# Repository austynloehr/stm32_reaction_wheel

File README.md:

# STM32 Reaction Wheel Development

This repo is used to store all development information for STM32 reaction wheel project.

## Components
- **MCU:** STM32F412CGU6
- **Motor:**  REV Neo 550 (Brushless)
- **Motor Controller:** VESC EDU
- **CAN Transceiver:** NXP TJA1051/T3
- **IMU:** MPU-6050
- **BLE:** HC-05

## Project Structure

- Hardware: All hardware design files for this project
    - Balance_Controller: All KiCAD design files  for controller PCB
    - Reaction_Wheel: All NX CAD files for this project
- Logs: Bluetooth data logs
- ReactionWheel_F412: STM32CubeIDE project, contains all code for MCU
    - Core: Core source code
    - Drivers: STM32 HAL drivers
    - Middlewares: External libraries
- Resources: Markdowns and datasheets
- Scripts: Scripts useful for design and data logging

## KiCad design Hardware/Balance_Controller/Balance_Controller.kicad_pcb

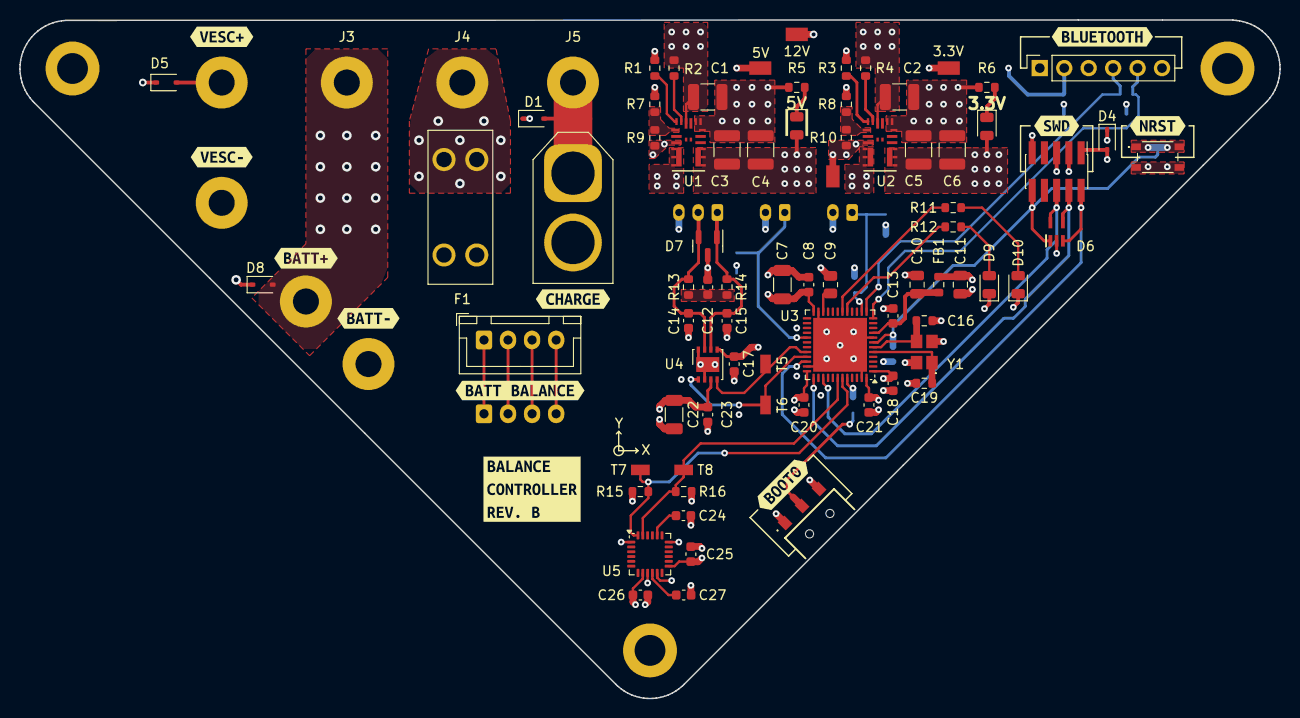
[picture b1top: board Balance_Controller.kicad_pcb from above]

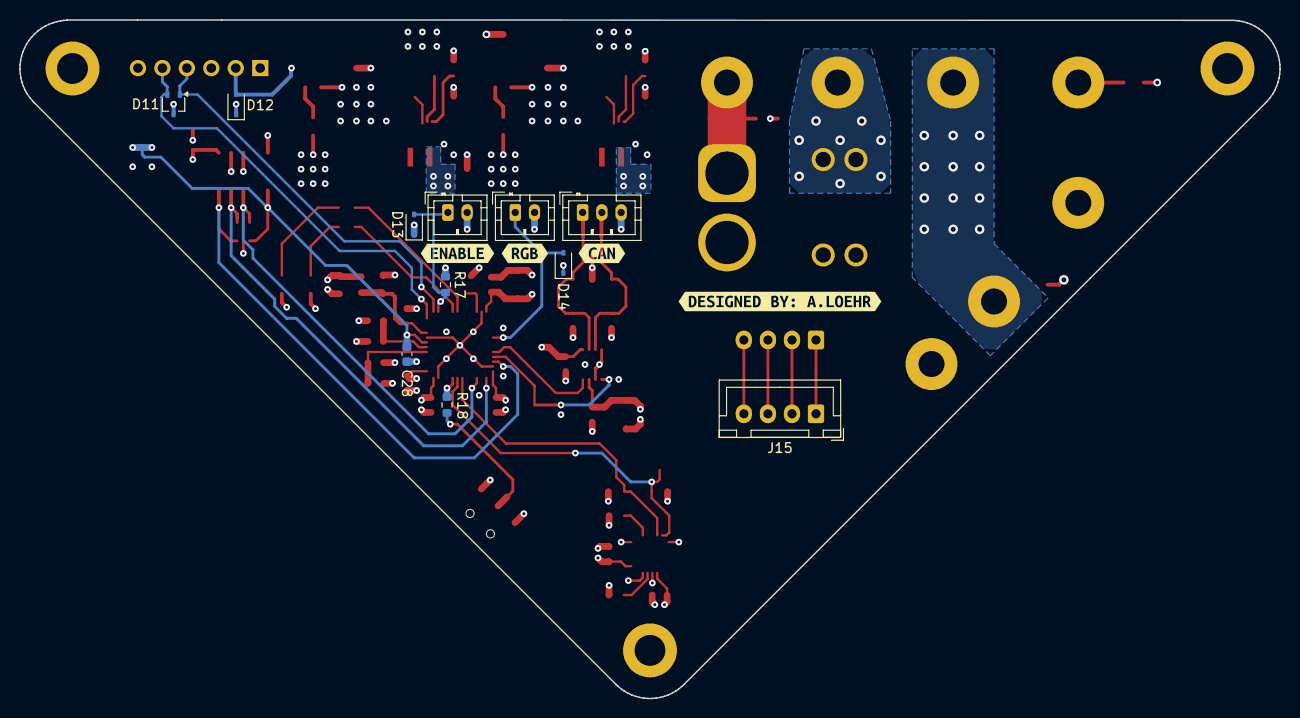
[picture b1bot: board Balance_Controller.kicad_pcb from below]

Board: 4 copper layers, 130.9 x 70.5 mm, 111 parts (15 on the bottom side), 46 nets.

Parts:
C1, C2, C3, C4, C5, C6: 22u; C_1210_3225Metric
C7, C22: 10u; C_1206_3216Metric
C8, C13, C17, C18, C20, C21, C25, C27, C28: 100n; C_0603_1608Metric
C9: 4.7u; R_0805_2012Metric
C10, C11: 1u; C_0805_2012Metric
C12, C23: 47n; C_0603_1608Metric
C14, C15: 100p; C_0603_1608Metric
C16, C19: 6p; R_0603_1608Metric
C24: 2.2n; C_0603_1608Metric
C26: 10n; C_0603_1608Metric
D1, D5, D8: D_TVS; D_SOD-323
D2, D3, D10: RED; LED_0805_2012Metric
D4, D12, D13, D14: SC1533-01FTG; D_SOD-323
D6: ESDALC6V1W5; SOT65P210X110-5N
D7: NUP2105L; SOT-23
D9: GRN; LED_0805_2012Metric
D11: VESD03A2-03G-G3-08; SOT-323_SC-70
F1: 20A; 3568
FB1: 120R; R_0603_1608Metric
H1, H2, H3: MountingHole_Pad; MountingHole_3.2mm_M3_DIN965_Pad
J1: HC-05; PinSocket_1x06_P2.54mm_Vertical
J2: VESC-; MountingHole_2.7mm_Pad
J3: COM_SW; MountingHole_2.7mm_Pad
J4: LOAD_SW; MountingHole_2.7mm_Pad
J5: CHRG_SW; MountingHole_2.7mm_Pad
J6: SWD; PinHeader_2x05_P1.27mm_Vertical_SMD
J7: CHARGE; AMASS_XT60-F_1x02_P7.20mm_Vertical
J8: VESC+; MountingHole_2.7mm_Pad
J9: BATT+; MountingHole_2.7mm_Pad
J10: BAL_BATT_A; JST_XH_B4B-XH-A_1x04_P2.50mm_Vertical
J11: BATT-; MountingHole_2.7mm_Pad
J12: ENABLE; JST_PH_B2B-PH-K_1x02_P2.00mm_Vertical
J13: RGB_LED; JST_PH_B2B-PH-K_1x02_P2.00mm_Vertical
J14: CAN; JST_PH_B3B-PH-K_1x03_P2.00mm_Vertical
J15: BAL_BATT_B; JST_XH_B4B-XH-A_1x04_P2.50mm_Vertical
R1: 53.6k; R_0603_1608Metric
R2, R4: 100k; R_0603_1608Metric
R3: 39k; R_0603_1608Metric
R5: 523; R_0603_1608Metric
R6, R11: 220; R_0603_1608Metric
R7: 34k; R_0603_1608Metric
R8: 40.2k; R_0603_1608Metric
R9: 6.49k; R_0603_1608Metric
R10: 12.7k; R_0603_1608Metric
R12: 15; R_0603_1608Metric
R13, R14: 60; R_0603_1608Metric
R15, R16: 4.7k; R_0603_1608Metric
R17, R18: 10k; R_0603_1608Metric
SW1: NRST; PTS815SJG250SMTRLFS
SW2: BOOT0; AYZ0102AURLC
T1, T2, T3, T4: TestPoint; RCT-0C
T5, T6, T7, T8: TestPoint; TP+195X110
U1, U2: MPM3610GQV-P; QFN3p0x5p0x1p6_MPM3610_MNP
U3: STM32F412CGU6; QFN-48-1EP_7x7mm_P0.5mm_EP5.6x5.6mm
U4: TJA1051TK-3; DFN-8-1EP_3x3mm_P0.65mm_EP1.55x2.4mm
U5: MPU-6050; InvenSense_QFN-24_4x4mm_P0.5mm
Y1: NX3225SA-16.000; NX3225SA16000MSTDCRS2
kibuzzard-1: G***; kibuzzard-65EC859F
kibuzzard-2: G***; kibuzzard-65EE22FE
kibuzzard-3: G***; kibuzzard-65C181EB
kibuzzard-4: G***; kibuzzard-65C183BF
kibuzzard-5: G***; kibuzzard-65C187BD
kibuzzard-6: G***; kibuzzard-65EE0D80
kibuzzard-7: G***; kibuzzard-65EBE841
kibuzzard-8: G***; kibuzzard-65C18803
kibuzzard-9: G***; kibuzzard-65C1883A
kibuzzard-10: G***; kibuzzard-65C18854
kibuzzard-11: G***; kibuzzard-65C185CB
kibuzzard-65EE6C62: G***; kibuzzard-65EE6C62
kibuzzard-65EE6C92: G***; kibuzzard-65EE6C92
kibuzzard-65EE6CA7: G***; kibuzzard-65EE6CA7
kibuzzard-65EE6CAC: G***; kibuzzard-65EE6CAC

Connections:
+3.3V: C5.1, C6.1, C7.1, C8.1, C11.1, C17.2, C18.1, C20.1, C21.1, C25.1, C26.1, D3.2 (A), D4.2 (A2), FB1.2, J6.1, R8.1, R15.2, R16.2, R17.2, SW2.3 (A), T3.1, U2.7 (OUT), U2.8 (OUT), U2.9 (OUT), U3.1 (VBAT), U3.24 (VDD), U3.36 (VDD), U3.48 (VDD), U4.5 (VIO), U5.8 (VLOGIC), U5.13 (VDD)
+3.3VA: C10.1, C13.1, FB1.1, U3.9 (VDDA)
+5V: C3.1, C4.1, C17.1, C22.1, C23.2, D2.2 (A), D12.2 (A2), J1.2, R7.1, T2.1, U1.7 (OUT), U1.8 (OUT), U1.9 (OUT), U4.3 (VCC)
+12V: C1.1, C2.1, D5.2 (A2), F1.1, F1.2, J8.1, R2.1, R4.1, T1.1, U1.16 (IN), U2.16 (IN)
/3.3V_FB: R8.2, R10.1, U2.1 (FB)
/3.3V_PWR_LED_K: D3.1 (K), R6.1
/5V_FB: R7.2, R9.1, U1.1 (FB)
/5V_PWR_LED_K: D2.1 (K), R5.1
/12V_FUSE: F1.3, F1.4, J4.1
/BOOT0: R18.1, U3.44 (BOOT0)
/CAN+: C14.1, D7.2 (K), J14.2, R13.1, U4.7 (CANH)
/CAN-: C15.1, D7.1 (K), J14.1, R14.2, U4.6 (CANL)
/CAN_RX: T5.1, U3.32 (PA11), U4.4 (RXD)
/CAN_TX: T6.1, U3.33 (PA12), U4.1 (TXD)
/ENABLE: D13.2 (A2), J12.1, R17.1, U3.14 (PA4)
/HSE_IN: C19.1, U3.5 (PH0), Y1.1
/HSE_OUT: C16.1, U3.6 (PH1), Y1.3
/LED_G: R12.1, U3.17 (PA7)
/LED_R: R11.1, U3.18 (PB0)
/NRST: C28.1, D6.1 (IO1), J6.10, SW1.1, SW1.2, U3.7 (NRST)
/PWM: D14.2 (A2), J13.1, U3.29 (PA8)
/SCL: R16.1, T8.1, U3.42 (PB6), U5.23 (SCL)
/SDA: R15.1, T7.1, U3.43 (PB7), U5.24 (SDA)
/SW0: D6.5 (IO4), J6.6, U3.39 (PB3)
/SWCLK: D6.4 (IO3), J6.4, U3.37 (PA14)
/SWIO: D6.3 (IO2), J6.2, U3.34 (PA13)
/UART_RX: D11.1 (IO1), J1.4, U3.13 (PA3)
/UART_TX: D11.2 (IO2), J1.5, U3.12 (PA2)
/VBAT: D8.2 (A2), J3.1, J9.1
/VCAP: C9.1, U3.22 (VCAP_1)
/VCHRG: D1.2 (A2), J5.1, J7.1
GND: C1.2, C2.2, C3.2, C4.2, C5.2, C6.2, C7.2, C8.2, C9.2, C10.2, C11.2, C12.1, C13.2, C14.2, C15.2, C16.2, C18.2, C19.2, C20.2, C21.2, C22.2, C23.1, C24.2, C25.2, C26.2, C27.2, C28.2, D1.1 (A1), D4.1 (A1), D5.1 (A1), D6.2 (GND), D7.3 (A), D8.1 (A1), D9.1 (K), D10.1 (K), D11.3 (GND), D12.1 (A1), D13.1 (A1), D14.1 (A1), H1.1, H2.1, H3.1, J1.3, J2.1, J6.3, J6.5, J6.9, J7.2, J11.1, J12.2, J13.2, J14.3, R1.2, R3.2, R5.2, R6.2, R9.2, R10.2, SW1.3, SW1.4, SW2.1 (C), T4.1, U1.3 (AGND), U1.12 (PGND), U1.13 (PGND), U1.14 (PGND), U2.3 (AGND), U2.12 (PGND), U2.13 (PGND), U2.14 (PGND), U3.8 (VSSA), U3.23 (VSS), U3.35 (VSS), U3.47 (VSS), U3.49 (VSS), U4.2 (GND), U4.8 (S), U4.9 (GND), U5.1 (CLKIN), U5.9 (AD0), U5.11 (FSYNC), U5.18 (GND), Y1.2, Y1.4
unnamed: C12.2, R13.2, R14.1
unnamed: D9.2 (A), R12.2
unnamed: D10.2 (A), R11.2
unnamed: J10.1, J15.1
unnamed: J10.2, J15.2
unnamed: J10.3, J15.3
unnamed: J10.4, J15.4
unnamed: R18.2, SW2.2 (B)
unnamed: R1.1, U1.18 (AAM)
unnamed: R2.2, U1.17 (EN)
unnamed: R3.1, U2.18 (AAM)
unnamed: R4.2, U2.17 (EN)
unnamed: C24.1, U5.20 (CPOUT)
unnamed: C27.1, U5.10 (REGOUT)

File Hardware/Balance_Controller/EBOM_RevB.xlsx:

Balance Controller EBOM (Rev. B)
# | Designator | Qty | Value | Footprint | Mfg Part # | Manufacturer
1 | C9 | 1 | 4.7u | Resistor_SMD:R_0805_2012Metric | GRM21BZ71E475KE15L | Murata
2 | C24 | 1 | 2.2n | Capacitor_SMD:C_0603_1608Metric | GRT1885C1H222JA02D | Murata
3 | C26 | 1 | 10n | Capacitor_SMD:C_0603_1608Metric | GRM1885C1H103JA01J | Murata
4 | D6 | 1 | ESDALC6V1W5 | ESDALC6V1W5:SOT65P210X110-5N | ESDALC6V1W5 | ST
5 | D7 | 1 | NUP2105L | Package_TO_SOT_SMD:SOT-23 | NUP2105L | Diotec
6 | D9 | 1 | GRN | LED_SMD:LED_0805_2012Metric | 150080GS75000 | Wurth Elektronik
7 | D11 | 1 | VESD03A2-03G-G3-08 | Package_TO_SOT_SMD:SOT-323_SC-70 | VESD03A2-03G-G3-08 | Vishay
8 | F1 | 1 | 20A | 534-3568:3568 | 3568 | Keystone Electronics
9 | FB1 | 1 | 120R | Resistor_SMD:R_0603_1608Metric | BLM18KG121TN1D | Murata
10 | J1 | 1 | HC-05 | Connector_PinSocket_2.54mm:PinSocket_1x06_P2.54mm_Vertical | 61300611821 | Wurth Elektronik
11 | J6 | 1 | SWD | Connector_PinHeader_1.27mm:PinHeader_2x05_P1.27mm_Vertical_SMD | FTSH-105-01-LM-DV-K-P-TR | Samtec
12 | J7 | 1 | CHARGE | Connector_AMASS:AMASS_XT60-F_1x02_P7.20mm_Vertical | XT60-F | AMASS
13 | J10 | 1 | BAL_BATT_A | Connector_JST:JST_XH_B4B-XH-A_1x04_P2.50mm_Vertical | B4B-XH-A | JST
14 | J12 | 1 | ENABLE | Connector_JST:JST_PH_B2B-PH-K_1x02_P2.00mm_Vertical | B2B-PH-K | JST
15 | J13 | 1 | RGB_LED | Connector_JST:JST_PH_B2B-PH-K_1x02_P2.00mm_Vertical | B2B-PH-K | JST
16 | J14 | 1 | CAN | Connector_JST:JST_PH_B3B-PH-K_1x03_P2.00mm_Vertical | B3B-PH-K | JST
17 | J15 | 1 | BAL_BATT_B | Connector_JST:JST_XH_B4B-XH-A_1x04_P2.50mm_Vertical | B4B-XH-A | JST
18 | R1 | 1 | 53.6k | Resistor_SMD:R_0603_1608Metric | ERJ-PA3F5362V | Panasonic
19 | R3 | 1 | 39k | Resistor_SMD:R_0603_1608Metric | ERJ-UP3J393V | Panasonic
20 | R5 | 1 | 523 | Resistor_SMD:R_0603_1608Metric | ERJ-PA3F5230V | Panasonic
21 | R7 | 1 | 34k | Resistor_SMD:R_0603_1608Metric | ERJ-PB3D3402V | Panasonic
22 | R8 | 1 | 40.2k | Resistor_SMD:R_0603_1608Metric | RCS060340K2FKEA | Vishay
23 | R9 | 1 | 6.49k | Resistor_SMD:R_0603_1608Metric | ERJ-PA3F6491V | Panasonic
24 | R10 | 1 | 12.7k | Resistor_SMD:R_0603_1608Metric | CRCW060312K7FKEAHP | Vishay
25 | R12 | 1 | 15 | Resistor_SMD:R_0603_1608Metric | ERJ-UP3F15R0V | Panasonic
26 | SW1 | 1 | NRST | PTS815_SJG_250_SMTR_LFS:PTS815SJG250SMTRLFS | PTS815 SJG 250 SMTR LFS | C&K
27 | SW2 | 1 | BOOT0 | AYZ0102AURLC:AYZ0102AURLC | AYZ0102AURLC | C&K
28 | U3 | 1 | STM32F412CGU6 | STM32F412:QFN-48-1EP_7x7mm_P0.5mm_EP5.6x5.6mm | STM32F412CGU6 | ST
29 | U4 | 1 | TJA1051TK-3 | Package_DFN_QFN:DFN-8-1EP_3x3mm_P0.65mm_EP1.55x2.4mm | TJA1051TK/3,118 | NXP
30 | U5 | 1 | MPU-6050 | MPU6050:InvenSense_QFN-24_4x4mm_P0.5mm | MPU-6050 | TDK InvenSense
31 | Y1 | 1 | NX3225SA-16.000 | NX3225SA-16.000M-STD-CRS-2:NX3225SA16000MSTDCRS2 | NX3225SA-16.000M-STD-CRS-2 | NDK
32 | C7,C22 | 2 | 10u | Capacitor_SMD:C_1206_3216Metric | GRM31CR71E106MA12L | Murata
33 | C10,C11 | 2 | 1u | Capacitor_SMD:C_0805_2012Metric | GRM21BR71C105KA01K | Murata
34 | C12,C23 | 2 | 47n | Capacitor_SMD:C_0603_1608Metric | GCJ188R71C473KA01D | Murata
35 | C14,C15 | 2 | 100p | Capacitor_SMD:C_0603_1608Metric | GCM1885C1H101JA16J | Murata
36 | C16,C19 | 2 | 6p | Resistor_SMD:R_0603_1608Metric | GRM1885C2A6R0DA01D | Murata
37 | R2,R4 | 2 | 100k | Resistor_SMD:R_0603_1608Metric | ERJ-UP3F1003V | Panasonic
38 | R6,R11 | 2 | 220 | Resistor_SMD:R_0603_1608Metric | ERJ-UP3J221V | Panasonic
39 | R13,R14 | 2 | 60 | Resistor_SMD:R_0603_1608Metric | ERJ-UP3F60R4V | Panasonic
40 | R15,R16 | 2 | 4.7k | Resistor_SMD:R_0603_1608Metric | MCT0603MD4701BP500 | Vishay
41 | R17,R18 | 2 | 10k | Resistor_SMD:R_0603_1608Metric | ESR03EZPJ103 | ROHM
42 | U1,U2 | 2 | MPM3610GQV-P | QFN3p0x5p0x1p6_MPM3610_MNP | MPM3610GQV-P | Monolithic Power Systems
43 | D1,D5,D8 | 3 | D_TVS | Diode_SMD:D_SOD-323 | PJGBLC12CR100001 | Panjit
44 | D2,D3,D10 | 3 | RED | LED_SMD:LED_0805_2012Metric | 150080SS75000 | Wurth Elektronik
45 | D4,D12,D13,D14 | 4 | SC1533-01FTG | Diode_SMD:D_SOD-323 | SC1533-01FTG | Littelfuse
46 | T1,T2,T3,T4 | 4 | TestPoint | RCT-0C:RCT-0C | RCT-0C | TE
47 | T5,T6,T7,T8 | 4 | TestPoint | RCU-0C:TP+195X110 | RCU-0C | TE
48 | C1,C2,C3,C4,C5,C6 | 6 | 22u | Capacitor_SMD:C_1210_3225Metric | GRM32ER71E226KE15L | Murata
49 | C8,C13,C17,C18,C20,C21,C25,C27,C28 | 9 | 100n | Capacitor_SMD:C_0603_1608Metric | GRM188R72A104KA35J | Murata

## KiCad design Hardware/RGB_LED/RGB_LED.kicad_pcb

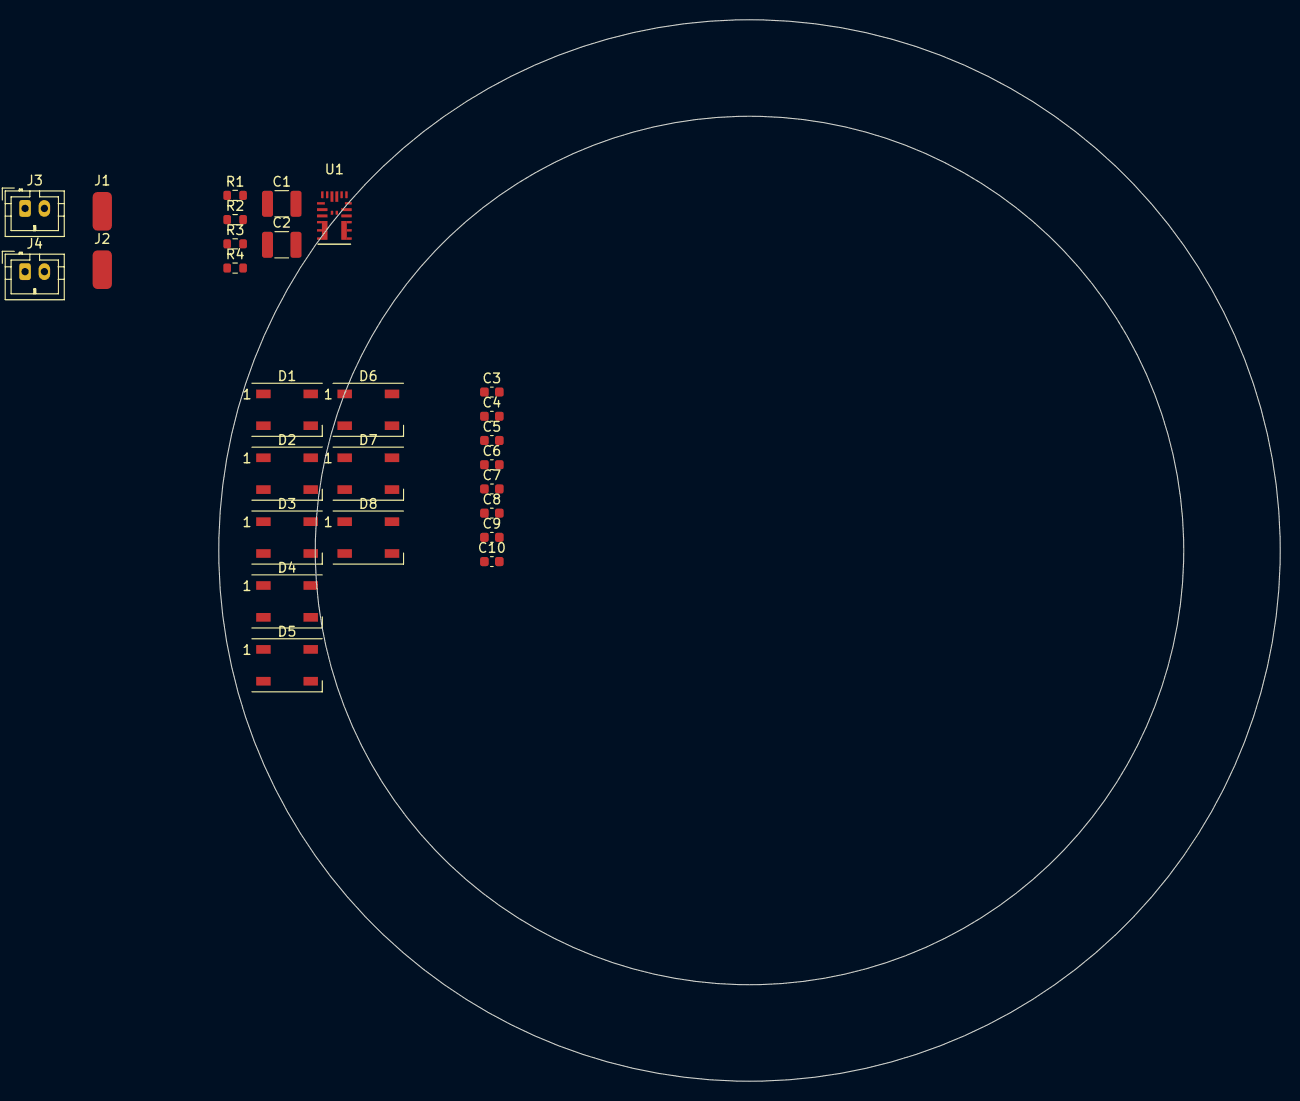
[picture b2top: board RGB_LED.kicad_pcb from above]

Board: 2 copper layers, 110.0 x 110.0 mm, 27 parts (0 on the bottom side), 15 nets, no tracks yet.

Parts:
C1, C2: 22u; C_1210_3225Metric
C3, C4, C5, C6, C7, C8, C9, C10: 15p; C_0603_1608Metric
D1, D2, D3, D4, D5, D6, D7, D8: WS2812B; LED_WS2812B_PLCC4_5.0x5.0mm_P3.2mm
J1: 12V; SolderWirePad_1x01_SMD_2x4mm
J2: GND; SolderWirePad_1x01_SMD_2x4mm
J3: DATA_IN; JST_PH_B2B-PH-K_1x02_P2.00mm_Vertical
J4: DATA_OUT; JST_PH_B2B-PH-K_1x02_P2.00mm_Vertical
R1, R2: 100k; R_0603_1608Metric
R3: 19.1k; R_0603_1608Metric
R4: 53.6k; R_0603_1608Metric
U1: MPM3610GQV-P; QFN3p0x5p0x1p6_MPM3610_MNP

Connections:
+5V: C2.1, C3.1, C4.1, C5.1, C6.1, C7.1, C8.1, C9.1, C10.1, D1.1 (VDD), D2.1 (VDD), D3.1 (VDD), D4.1 (VDD), D5.1 (VDD), D6.1 (VDD), D7.1 (VDD), D8.1 (VDD), R2.1, U1.7 (OUT), U1.8 (OUT), U1.9 (OUT)
+12V: C1.1, J1.1, R1.1, U1.16 (IN)
/5V_FB: R2.2, R3.1, U1.1 (FB)
/DIN: D1.4 (DIN), J3.1
/DOUT: D8.2 (DOUT), J4.1
GND: C1.2, C2.2, C3.2, C4.2, C5.2, C6.2, C7.2, C8.2, C9.2, C10.2, D1.3 (VSS), D2.3 (VSS), D3.3 (VSS), D4.3 (VSS), D5.3 (VSS), D6.3 (VSS), D7.3 (VSS), D8.3 (VSS), J2.1, J3.2, J4.2, R3.2, R4.2, U1.3 (AGND), U1.12 (PGND), U1.13 (PGND), U1.14 (PGND)
unnamed: D1.2 (DOUT), D2.4 (DIN)
unnamed: D2.2 (DOUT), D3.4 (DIN)
unnamed: D3.2 (DOUT), D4.4 (DIN)
unnamed: D4.2 (DOUT), D5.4 (DIN)
unnamed: D5.2 (DOUT), D6.4 (DIN)
unnamed: D6.2 (DOUT), D7.4 (DIN)
unnamed: D7.2 (DOUT), D8.4 (DIN)
unnamed: R4.1, U1.18 (AAM)
unnamed: R1.2, U1.17 (EN)

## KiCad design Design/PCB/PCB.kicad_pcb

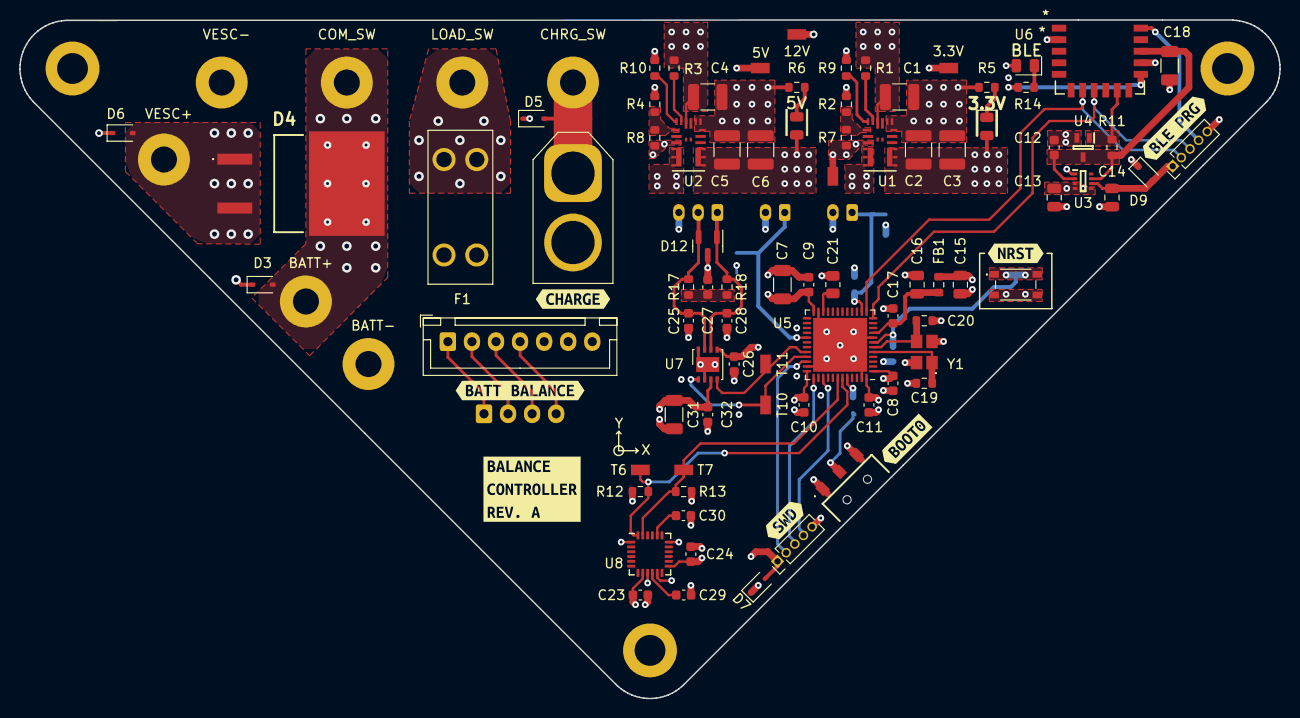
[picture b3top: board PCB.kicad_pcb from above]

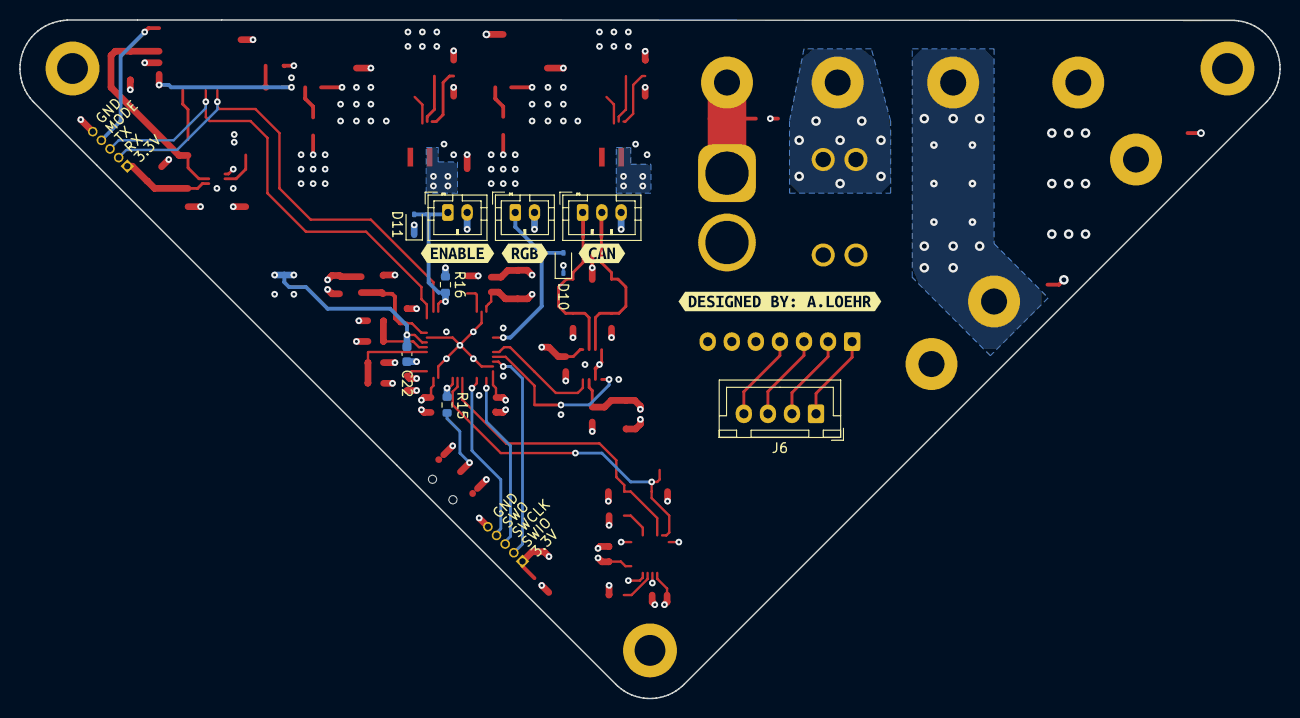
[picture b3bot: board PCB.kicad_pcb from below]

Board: 4 copper layers, 130.9 x 70.5 mm, 112 parts (13 on the bottom side), 48 nets.

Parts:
BATT BALANCE: BAL_CHRG; JST_XH_B7B-XH-A_1x07_P2.50mm_Vertical
BATT+: BATT+; MountingHole_2.7mm_Pad
BATT-: BATT-; MountingHole_2.7mm_Pad
C1, C2, C3, C4, C5, C6: 22u; C_1210_3225Metric
C7, C18, C31: 10u; C_1206_3216Metric
C8, C9, C10, C11, C12, C17, C22, C24, C26, C29: 100n; C_0603_1608Metric
C13, C14, C15, C16: 1u; C_0805_2012Metric
C19, C20: 6p; R_0603_1608Metric
C21: 4.7u; R_0805_2012Metric
C23: 10n; C_0603_1608Metric
C25, C28: 100p; C_0603_1608Metric
C27, C32: 47n; C_0603_1608Metric
C30: 2.2n; C_0603_1608Metric
CHARGE: CHARGE; AMASS_XT60-F_1x02_P7.20mm_Vertical
CHRG_SW: CHRG_SW; MountingHole_2.7mm_Pad
COM_SW: COM_SW; MountingHole_2.7mm_Pad
D1, D2: RED; LED_0805_2012Metric
D3, D5, D6: D_TVS; D_SOD-323
D4: REGEN_BYPASS; SBM3060VDCAU_R2_006A1
D7, D9, D10, D11: SC1533-01FTG; D_SOD-323
D8: BLUE; LED_0805_2012Metric
D12: NUP2105L; SOT-23
F1: 20A; 3568
FB1: 120R; R_0603_1608Metric
H1, H2, H3: MountingHole_Pad; MountingHole_3.2mm_M3_DIN965_Pad
J6: BAL_BATT; JST_XH_B4B-XH-A_1x04_P2.50mm_Vertical
J11: SWD; PinHeader_1x05_P1.27mm_Vertical
J12: BLE PROG; PinHeader_1x05_P1.27mm_Vertical
J13: RGB_LED; JST_PH_B2B-PH-K_1x02_P2.00mm_Vertical
J14: ENABLE; JST_PH_B2B-PH-K_1x02_P2.00mm_Vertical
J15: CAN; JST_PH_B3B-PH-K_1x03_P2.00mm_Vertical
LOAD_SW: LOAD_SW; MountingHole_2.7mm_Pad
R1, R3: 100k; R_0603_1608Metric
R2: 40.2k; R_0603_1608Metric
R4: 34k; R_0603_1608Metric
R5: 220; R_0603_1608Metric
R6: 523; R_0603_1608Metric
R7: 12.7k; R_0603_1608Metric
R8: 6.49k; R_0603_1608Metric
R9: 39k; R_0603_1608Metric
R10: 53.6k; R_0603_1608Metric
R11, R12, R13: 4.7k; R_0603_1608Metric
R14: 300; R_0603_1608Metric
R15, R16: 10k; R_0603_1608Metric
R17, R18: 60; R_0603_1608Metric
SW1: NRST; PTS815SJG250SMTRLFS
SW2: BOOT0; AYZ0102AURLC
T1, T2, T3, T4, T6, T7, T10, T11: TestPoint; TP+195X110
U1, U2: MPM3610GQV-P; QFN3p0x5p0x1p6_MPM3610_MNP
U3: TPS2116DRLR; SOTFL50P160X60-8N
U4: MCP111T-195I/LB; SOT65P210X110-3N
U5: STM32F412CGU6; QFN-48-1EP_7x7mm_P0.5mm_EP5.6x5.6mm
U6: RN4871-I/RM140; RN4871_MCH
U7: TJA1051TK-3; DFN-8-1EP_3x3mm_P0.65mm_EP1.55x2.4mm
U8: MPU-6050; InvenSense_QFN-24_4x4mm_P0.5mm
VESC+: VESC+; MountingHole_2.7mm_Pad
VESC-: VESC-; MountingHole_2.7mm_Pad
Y1: NX3225SA-16.000; NX3225SA16000MSTDCRS2
kibuzzard-65C181B2: G***; kibuzzard-65C181B2
kibuzzard-65C181EB: G***; kibuzzard-65C181EB
kibuzzard-65C183BF: G***; kibuzzard-65C183BF
kibuzzard-65C185CB: G***; kibuzzard-65C185CB
kibuzzard-65C185F9: G***; kibuzzard-65C185F9
kibuzzard-65C187BD: G***; kibuzzard-65C187BD
kibuzzard-65C1883A: G***; kibuzzard-65C1883A
kibuzzard-65C18164: G***; kibuzzard-65C18164
kibuzzard-65C18390: G***; kibuzzard-65C18390
kibuzzard-65C18803: G***; kibuzzard-65C18803
kibuzzard-65C18854: G***; kibuzzard-65C18854

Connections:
+3.3V: C2.1, C3.1, C7.1, C8.1, C9.1, C10.1, C11.1, C13.1, C15.1, C23.1, C24.1, C26.2, D1.2 (A), D7.2 (A2), FB1.2, J11.1, R2.1, R12.2, R13.2, R16.2, SW2.3 (A), T2.1, U1.7 (OUT), U1.8 (OUT), U1.9 (OUT), U3.3 (VI_1), U3.4 (PR1), U3.5 (MODE), U5.1 (VBAT), U5.24 (VDD), U5.36 (VDD), U5.48 (VDD), U7.5 (VIO), U8.8 (VLOGIC), U8.13 (VDD)
+3.3VA: C16.1, C17.1, FB1.1, U5.9 (VDDA)
+5V: C5.1, C6.1, C26.1, C31.1, C32.2, D2.2 (A), D8.2 (A), R4.1, T3.1, U2.7 (OUT), U2.8 (OUT), U2.9 (OUT), U7.3 (VCC)
+12V: C1.1, C4.1, D4.1 (A), D4.3 (A), D6.2 (A2), F1.1, F1.2, R1.1, R3.1, T1.1, U1.16 (IN), U2.16 (IN), VESC+.1
/3.3V_FB: R2.2, R7.1, U1.1 (FB)
/3.3V_PWR_LED_K: D1.1 (K), R5.1
/5V_FB: R4.2, R8.1, U2.1 (FB)
/5V_PWR_LED_K: D2.1 (K), R6.1
/12V_FUSE: F1.3, F1.4, LOAD_SW.1
/BLE_MODE: J12.4, U6.16 (P2_0)
/BLE_NRST: R11.1, U4.1 (VOUT), U6.10 (RST_N)
/BLE_ON_LED_K: R14.2, U6.12 (P0_2)
/BOOT0: R15.1, U5.44 (BOOT0)
/CAN+: C25.1, D12.2 (K), J15.2, R17.1, U7.7 (CANH)
/CAN-: C28.1, D12.1 (K), J15.1, R18.2, U7.6 (CANL)
/CAN_RX: T11.1, U5.32 (PA11), U7.4 (RXD)
/CAN_TX: T10.1, U5.33 (PA12), U7.1 (TXD)
/ENABLE: D11.2 (A2), J14.1, R16.1, U5.14 (PA4)
/HSE_IN: C19.1, U5.5 (PH0), Y1.1
/HSE_OUT: C20.1, U5.6 (PH1), Y1.3
/NRST: C22.1, SW1.1, SW1.2, U5.7 (NRST)
/PWM: D10.2 (A2), J13.1, U5.29 (PA8)
/SCL: R13.1, T7.1, U5.42 (PB6), U8.23 (SCL)
/SDA: R12.1, T6.1, U5.43 (PB7), U8.24 (SDA)
/SW0: J11.4, U5.39 (PB3)
/SWCLK: J11.3, U5.37 (PA14)
/SWIO: J11.2, U5.34 (PA13)
/UART_RX: J12.2, U5.13 (PA3), U6.7 (UART_RX)
/UART_TX: J12.3, U5.12 (PA2), U6.8 (UART_TX)
/VBAT: BATT+.1, COM_SW.1, D3.2 (A2), D4.2 (K)
/VBLE: C12.1, C18.1, R11.2, U3.2 (VO_1), U3.7 (VO_2), U4.3 (VDD), U6.14 (VBAT)
/VCAP: C21.1, U5.22 (VCAP_1)
/VCHRG: CHARGE.1, CHRG_SW.1, D5.2 (A2)
/VPROG: C14.1, D9.2 (A2), J12.1, U3.6 (VI_2)
GND: BATT-.1, C1.2, C2.2, C3.2, C4.2, C5.2, C6.2, C7.2, C8.2, C9.2, C10.2, C11.2, C12.2, C13.2, C14.2, C15.2, C16.2, C17.2, C18.2, C19.2, C20.2, C21.2, C22.2, C23.2, C24.2, C25.2, C27.1, C28.2, C29.2, C30.2, C31.2, C32.1, CHARGE.2, D3.1 (A1), D5.1 (A1), D6.1 (A1), D7.1 (A1), D9.1 (A1), D10.1 (A1), D11.1 (A1), D12.3 (A), H1.1, H2.1, H3.1, J11.5, J12.5, J13.2, J14.2, J15.3, R5.2, R6.2, R7.2, R8.2, R9.2, R10.2, SW1.3, SW1.4, SW2.1 (C), T4.1, U1.3 (AGND), U1.12 (PGND), U1.13 (PGND), U1.14 (PGND), U2.3 (AGND), U2.12 (PGND), U2.13 (PGND), U2.14 (PGND), U3.1 (GND), U4.2 (VSS), U5.8 (VSSA), U5.23 (VSS), U5.35 (VSS), U5.47 (VSS), U5.49 (VSS), U6.2 (GND), U6.13 (GND), U7.2 (GND), U7.8 (S), U7.9 (GND), U8.1 (CLKIN), U8.9 (AD0), U8.11 (FSYNC), U8.18 (GND), VESC-.1, Y1.2, Y1.4
unnamed: C27.2, R17.2, R18.1
unnamed: D8.1 (K), R14.1
unnamed: BATT BALANCE.1, J6.1
unnamed: BATT BALANCE.2, J6.2
unnamed: BATT BALANCE.3, J6.3
unnamed: BATT BALANCE.4, J6.4
unnamed: R15.2, SW2.2 (B)
unnamed: R9.1, U1.18 (AAM)
unnamed: R1.2, U1.17 (EN)
unnamed: R10.1, U2.18 (AAM)
unnamed: R3.2, U2.17 (EN)
unnamed: C30.1, U8.20 (CPOUT)
unnamed: C29.1, U8.10 (REGOUT)

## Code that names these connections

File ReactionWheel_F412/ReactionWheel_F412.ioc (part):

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Mcu.Name=STM32F412C(E-G)Ux
Mcu.Package=UFQFPN48
Mcu.UserName=STM32F412CGUx
PA11.Mode=CAN_Activate
PA11.Signal=CAN1_RX
PA12.Mode=CAN_Activate
PA12.Signal=CAN1_TX
PA13.Mode=Trace_Asynchronous_SW
PA13.Signal=SYS_JTMS-SWDIO
PA14.Mode=Trace_Asynchronous_SW
PA14.Signal=SYS_JTCK-SWCLK
PA2.Mode=Asynchronous
PA2.Signal=USART2_TX
PA3.Mode=Asynchronous
PA3.Signal=USART2_RX
PA4.GPIOParameters=GPIO_Label
PA4.GPIO_Label=EnableBtn
PA4.Signal=GPIO_Input
PA7.GPIOParameters=GPIO_Speed,PinState,GPIO_PuPd,GPIO_Label,GPIO_ModeDefaultOutputPP
PA7.GPIO_Label=GLED
PA7.GPIO_ModeDefaultOutputPP=GPIO_MODE_OUTPUT_PP
PA7.GPIO_PuPd=GPIO_PULLDOWN
PA7.GPIO_Speed=GPIO_SPEED_FREQ_HIGH
PA7.PinState=GPIO_PIN_RESET
PA7.Signal=GPIO_Output
PA8.GPIOParameters=GPIO_Label
PA8.GPIO_Label=PWM_LED
PA8.Signal=S_TIM1_CH1
PB0.GPIOParameters=GPIO_Speed,PinState,GPIO_PuPd,GPIO_Label
PB0.GPIO_Label=RLED
PB0.GPIO_PuPd=GPIO_PULLDOWN
PB0.GPIO_Speed=GPIO_SPEED_FREQ_HIGH
PB0.PinState=GPIO_PIN_RESET
PB0.Signal=GPIO_Output
PB3.Mode=Trace_Asynchronous_SW
PB3.Signal=SYS_JTDO-SWO
PB6.Mode=I2C
PB6.Signal=I2C1_SCL
PB7.Mode=I2C
PB7.Signal=I2C1_SDA
PH0\ -\ OSC_IN.Mode=HSE-External-Oscillator
PH0\ -\ OSC_IN.Signal=RCC_OSC_IN
PH1\ -\ OSC_OUT.Mode=HSE-External-Oscillator
PH1\ -\ OSC_OUT.Signal=RCC_OSC_OUT
RCC.HSE_VALUE=16000000
RCC.SYSCLKFreq_VALUE=100000000
RCC.SYSCLKSource=RCC_SYSCLKSOURCE_PLLCLK
board=custom

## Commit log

2023-07-19 Initial commit with working build and updated architecture
2023-07-21 Added working test software to main firmware structure.
2023-08-06 Committing progress
2023-08-15 Added link for VirtualEnvWrapper setup
2023-08-20 Remade project after computer reset. Updated script documation.
2023-08-23 Completed ComplimentaryFilter python testing
2023-08-23 Adding some test log files
2023-09-21 Impletmented real-time complimentary filter for MPU6050 data
2023-09-28 Added Schematic.drawio
2023-09-28 Created baseline schematic
2023-09-29 Added power and motor control to schematics
2023-10-01 Added datasheets for chosen motor and motor controller.
2023-10-03 Designed initial test schematic.drawio
2023-10-03 Configured outputs for test motor setup
2023-10-12 Organized Resources folder
2023-10-18 Created inverted pendulum simulink model
2023-11-18 Added docs for new motor and controller. Added some logic to control initialization angle and gyro reset angle.
2023-11-18 Moved location of new motor and controller Datasheets
2023-11-20 Got code working for new STM32F407 project
2023-11-24 Added CANalyzer project files
2023-12-05 Created VESC CAN driver. Added functionality to drive with IMU.
2023-12-05 Added F407 eval board Datasheet
2023-12-05 Updated main README
2023-12-05 Added simulink changes
2023-12-05 Updated architecture diagrams
2023-12-05 Added docs for new motor and controller. Added some logic to control initialization angle and gyro reset angle.
    Added STM32_Reaction_Wheel_Architecture.drawio.png
    Added STM32_Reaction_Wheel_Architecture-IO.drawio.png
    Added STM32_Reaction_Wheel_Architecture-IO.drawio.png
    Update STM32_Reaction_Wheel_Architecture.drawio
    Update STM32_Reaction_Wheel_Architecture.drawio
2023-12-05 Feature/4 develop motor controller api (#13)
    * Organized Resources folder
    * Created inverted pendulum simulink model
    * Added docs for new motor and controller. Added some logic to control initialization angle and gyro reset angle.
    * Moved location of new motor and controller Datasheets
    * Got code working for new STM32F407 project
    * Added CANalyzer project files
2023-12-25 Checking in prototype desgn progress
2023-12-25 Added WS2812 testing code
2024-01-06 Completed first pass at PCB schematic
2024-01-06 Schematic formatting clean up, added TVS diode to LED PWM
2024-01-12 Schematic revisions after review
2024-02-04 First pass at PCB layout and routing
2024-02-08 Added final pcb design and manufacturing files
2024-02-08 Moved old firmware to testing folder
2024-02-08 Updated README for latest hardware
2024-02-08 Feature/14 pcb design (#16)
    * Checking in prototype desgn progress
    * Completed first pass at PCB schematic
    * Schematic formatting clean up, added TVS diode to LED PWM
    * Schematic revisions after review
    * First pass at PCB layout and routing
    * Added final pcb design and manufacturing files
2024-02-11 Renamed pcb files and moved to Hardware folder. Cleaned up component paths.
2024-03-09 Ported code to F12
2024-03-09 Added LED board progress
2024-03-11 Updated schematic and routing
2024-03-12 Created updated BOM and manufacturing files
2024-03-23 Updated XT60 PN and added render
2024-03-23 17 revise balance controller pcb (#18)
    * Added LED board progress
    * Updated schematic and routing
    * Created updated BOM and manufacturing files
    * Updated XT60 PN and added render
2024-03-23 Created 3D model for Balance Controller
2024-03-23 Created lighter weight CAD model for Balance_Controller
2024-03-23 Checkin battery bracket progress
2024-05-22 Added simulink files and code for state machines
2024-05-24 Removed atomic subsystem from primary PrimaryStateMachine
2024-05-24 Ported simulink state machines to target
2024-05-24 Added screenshots of StateFlow diagrams
2024-06-18 Added debug to gitignore. Checking in balance control progress.
2024-09-30 Added ability to read binary data instead of strings over UART. Added connection to influx.
2024-10-03 Reduced UART baud rate to 480600, fixed issue with binary logger reporting incorrect data
2024-10-03 Adding characterization log files for kalman filter
2024-11-08 Checking in progress on C kalmanFilter
2024-11-13 Checking in working MCU kalman filter
2024-12-26 Redesigned chassis for version 3
2024-12-26 Removed design folder
2024-12-26 Feature/7 design and 3d print prototype chassis (#19)
    * Checking in prototype desgn progress
    * Checkin battery bracket progress
    * Redesigned chassis for version 3
    * Removed design folder
2024-12-26 Checking in work before merge
2025-01-02 Balance controller tuned with base settings, logger updated for additional data
2025-01-02 Finished balance tuning, repo cleanup
2025-01-02 Removed Simulink file tracking
2025-01-02 Feature/5 implement balance control (#20)
    * Added Schematic.drawio
    * Created baseline schematic
    * Added power and motor control to schematics
    * Added datasheets for chosen motor and motor controller.
    * Designed initial test schematic.drawio
    * Configured outputs for test motor setup
2025-01-02 Updated script and HC05 Markdowns
2025-01-03 Updated MCU datasheet
2025-02-07 Create LICENSE
2025-02-07 Update LICENSE
2025-02-18 Update kalman gains
2025-10-04 Read logging frame format from yaml file. Can read and unpack bt log frames.
2025-10-04 stopped tracking log files in git
2025-10-04 Can now log data to parquet file to later viewing
2025-10-04 Moved logging frame description to src near CT_logging.
2025-10-05 Added functionality to view live data and logs in rerun
2025-10-05 Force error if serial port cant open
2025-12-26 Initial cargo project layout
2025-12-30 First pass at IMU task
2025-12-30 Update firmware readme
2025-12-30 Adding firmware build pipeline
2025-12-30 Update to use github actions
2025-12-30 Created release pipeline
2025-12-31 Refactor for easier host testing
2025-12-31 move testing piples step before build
2025-12-31 Rename piplines
2025-12-31 Remove redundant files
2025-12-31 Reading motor CAN data inside task
2026-01-01 Created unit tests for vesc driver
2026-01-02 Cache libudev in pipeline
2026-01-02 Zip artifacts in pipeline
2026-01-02 Update outdated dependencies
2026-01-02 Remove manual zip
2026-01-02 Test gpush
2026-01-02 Test gpush again
2026-01-02 test commit
2026-01-03 Imu task tested on target
2026-01-03 Fix clippy error
2026-01-04 CAN refactored and READ working
2026-01-05 Improved CAN startup behavior
2026-01-06 LED driver tested
2026-01-08 Refactor to use embassy CAN frame type instead of custom type
2026-01-08 Improve error handling throughout current progress
2026-01-09 Created task rate monitor macro
2026-01-09 Add startup delay to task monitor macro
2026-01-09 Button task working
2026-01-11 Clean up types and signal access
